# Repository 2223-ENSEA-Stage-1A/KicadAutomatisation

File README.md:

# KicadAutomatisation
Tous les scripts pour les automatisations kicad

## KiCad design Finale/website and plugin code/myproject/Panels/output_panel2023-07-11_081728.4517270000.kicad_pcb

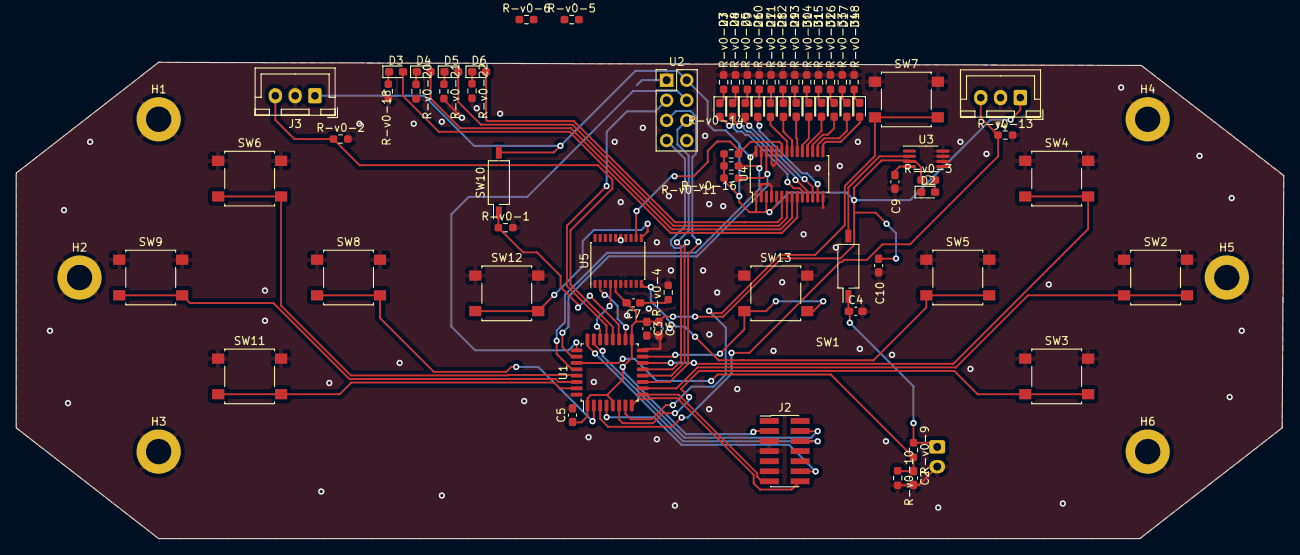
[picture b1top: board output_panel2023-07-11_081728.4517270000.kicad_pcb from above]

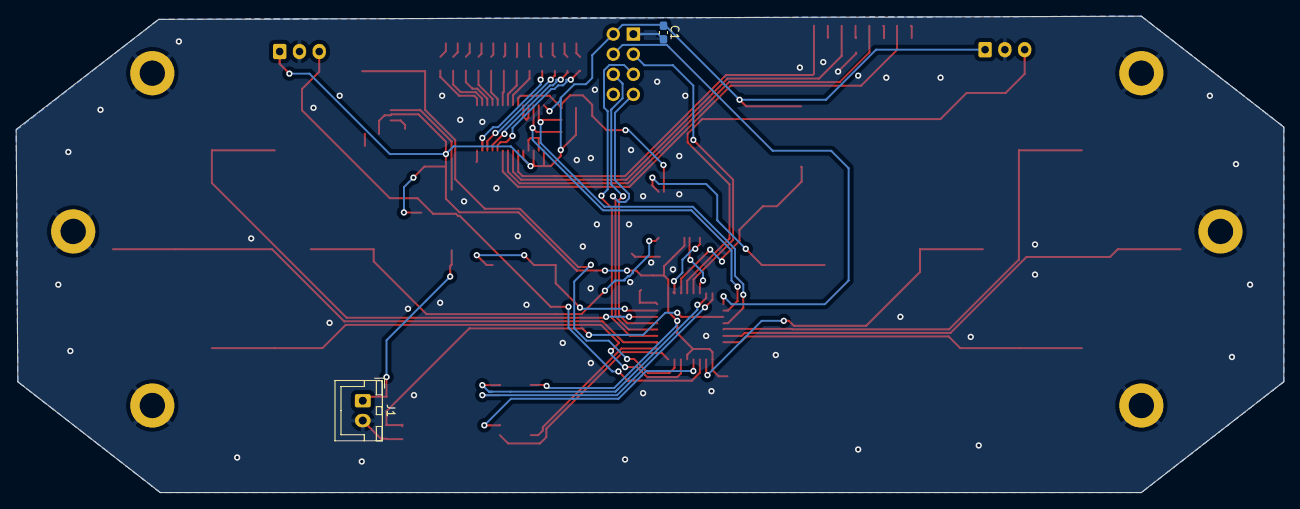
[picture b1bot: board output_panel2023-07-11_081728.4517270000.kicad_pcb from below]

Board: 2 copper layers, 160.2 x 60.2 mm, 82 parts (2 on the bottom side), 69 nets.

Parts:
C1: 100uF; C_0603_1608Metric_Pad1.08x0.95mm_HandSolder
C2: 1nF; C_0603_1608Metric_Pad1.08x0.95mm_HandSolder
C3, C5: 100n; C_0603_1608Metric_Pad1.08x0.95mm_HandSolder
C4: 1u; C_0603_1608Metric_Pad1.08x0.95mm_HandSolder
C6: 10u; C_0603_1608Metric_Pad1.08x0.95mm_HandSolder
C7: 100µF; C_0603_1608Metric_Pad1.08x0.95mm_HandSolder
C9: 470p; C_0603_1608Metric_Pad1.08x0.95mm_HandSolder
C10: 100nF; C_0603_1608Metric_Pad1.08x0.95mm_HandSolder
D2: L-v0-ED_Small; L-v0-ED_0603_1608Metric_Pad1.05x0.95mm_HandSolder
D3: G1; L-v0-ED_0603_1608Metric_Pad1.05x0.95mm_HandSolder
D4: G2; L-v0-ED_0603_1608Metric_Pad1.05x0.95mm_HandSolder
D5: G3; L-v0-ED_0603_1608Metric_Pad1.05x0.95mm_HandSolder
D6: G4; L-v0-ED_0603_1608Metric_Pad1.05x0.95mm_HandSolder
D7: G5; L-v0-ED_0603_1608Metric_Pad1.05x0.95mm_HandSolder
D8: G6; L-v0-ED_0603_1608Metric_Pad1.05x0.95mm_HandSolder
D9: G7; L-v0-ED_0603_1608Metric_Pad1.05x0.95mm_HandSolder
D10: G8; L-v0-ED_0603_1608Metric_Pad1.05x0.95mm_HandSolder
D11: O1; L-v0-ED_0603_1608Metric_Pad1.05x0.95mm_HandSolder
D12: O2; L-v0-ED_0603_1608Metric_Pad1.05x0.95mm_HandSolder
D13: O3; L-v0-ED_0603_1608Metric_Pad1.05x0.95mm_HandSolder
D14: O4; L-v0-ED_0603_1608Metric_Pad1.05x0.95mm_HandSolder
D15: R-v0-1; L-v0-ED_0603_1608Metric_Pad1.05x0.95mm_HandSolder
D16: R-v0-2; L-v0-ED_0603_1608Metric_Pad1.05x0.95mm_HandSolder
D17: R-v0-3; L-v0-ED_0603_1608Metric_Pad1.05x0.95mm_HandSolder
D18: R-v0-4; L-v0-ED_0603_1608Metric_Pad1.05x0.95mm_HandSolder
H1, H2, H3, H4, H5, H6: MountingHole_Pad; MountingHole_3.2mm_M3_DIN965_Pad
J1: Conn_01x02; JST_XH_B2B-XH-A_1x02_P2.50mm_Vertical
J2: Conn_02x07_Odd_Even; PinHeader_2x07_P1.27mm_Vertical_SMD
J3, J4: Conn_01x03; JST_XH_B3B-XH-A_1x03_P2.50mm_Vertical
R-v0-1, R-v0-2, R-v0-3, R-v0-5, R-v0-6, R-v0-13, R-v0-18, R-v0-20, R-v0-21, R-v0-22, R-v0-23, R-v0-24, R-v0-25, R-v0-26, R-v0-27, R-v0-28, R-v0-29, R-v0-30, R-v0-31, R-v0-32, R-v0-33, R-v0-34: 1K; R-v0-_0603_1608Metric_Pad0.98x0.95mm_HandSolder
R-v0-4: 10k; R-v0-_0603_1608Metric_Pad0.98x0.95mm_HandSolder
R-v0-9, R-v0-10: 1M; R-v0-_0603_1608Metric_Pad0.98x0.95mm_HandSolder
R-v0-11, R-v0-14, R-v0-16: 10K; R-v0-_0603_1608Metric_Pad0.98x0.95mm_HandSolder
SW1, SW10: SW_DIP_x01; SW_DIP_SPSTx01_Slide_Copal_CHS-01B_W7.62mm_P1.27mm
SW2, SW3, SW4, SW5, SW6, SW8, SW9, SW11, SW12, SW13: SW_Push; SW_SPST_B3S-1000
SW7: SW_SPST; SW_SPST_B3S-1000
U1: STM32L-v0-412KBTx; L-v0-QFP-32_7x7mm_P0.8mm
U2: nR-v0-F24_Full; PinHeader_2x04_P2.54mm_Vertical
U3: MIC5219-3.3YMM; MSOP-8_3x3mm_P0.65mm
U4: PCA9685PW; TSSOP-28_4.4x9.7mm_P0.65mm
U5: PCF8574TS; SSOP-20_4.4x6.5mm_P0.65mm

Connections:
A_Button-v0-: SW2.2, U1.10 (PA4)
B_Button-v0-: SW3.2, U1.6 (PA0)
CSN_nR-v0-F24: U1.25 (PA15), U2.4 (CSN)
DC_Button-v0-: SW11.2, U1.31 (PH3)
DIODE_CL-v0-K: R-v0-14.2, U1.26 (PB3), U4.26 (SCL-v0-)
DIODE_OE-v0-: R-v0-16.1, U4.23 (~OE), U5.12 (P2)
DIODE_SDA-v0-: R-v0-11.1, U1.28 (PB5), U4.27 (SDA)
Digital_Out_Put-v0-: U1.12 (PA6), U2.7 (MISO)
GND-v0-: C1.2, C2.2, C3.2, C4.2, C5.2, C6.2, C9.2, C10.2, D2.1 (K), H1.1, H2.1, H3.1, H4.1, H5.1, H6.1, J1.2, J2.5, J2.7, J2.11, J3.2, J4.2, R-v0-1.2, R-v0-2.2, R-v0-4.2, R-v0-10.2, R-v0-13.2, R-v0-18.2, R-v0-20.2, R-v0-21.2, R-v0-22.2, R-v0-23.2, R-v0-24.2, R-v0-25.2, R-v0-26.2, R-v0-27.2, R-v0-28.2, R-v0-29.2, R-v0-30.2, R-v0-31.2, R-v0-32.2, R-v0-33.2, R-v0-34.2, SW2.1, SW3.1, SW4.1, SW5.1, SW6.1, SW7.1 (A), SW8.1, SW9.1, SW11.1, SW12.1, SW13.1, U1.16 (VSS), U1.32 (VSS), U2.1 (GND-v0-), U3.5 (GND-v0-), U3.6 (GND-v0-), U3.7 (GND-v0-), U3.8 (GND-v0-), U4.2 (A1), U4.4 (A3), U4.14 (VSS), U4.24 (A5), U4.25 (EXTCL-v0-K), U5.1 (~INT), U5.6 (A0), U5.7 (A1), U5.9 (A2), U5.15 (VSS)
GPIO_EX_CL-v0-K: R-v0-5.2, U1.18 (PA8), U5.2 (SCL-v0-)
GPIO_EX_SER-v0-IAL-v0-_DATA: R-v0-6.2, U1.22 (PA12), U5.4 (SDA)
Glob_Alim-v0-: C1.1, C3.1, C5.1, C6.1, C7.2, C10.1, J2.3, J3.1, J4.1, R-v0-3.1, R-v0-5.1, R-v0-6.1, R-v0-11.2, R-v0-14.1, R-v0-16.2, SW10.2, U1.1 (VDD), U1.5 (VDDA), U1.17 (VDD), U2.2 (VCC), U3.3 (OUT), U4.1 (A0), U4.3 (A2), U4.5 (A4), U4.28 (VDD), U5.5 (VDD)
L-v0-: J4.3, R-v0-13.1, U1.3 (PC15)
L-v0-C_Button-v0-: SW8.2, U1.2 (PC14)
L-v0-i-ion-v0-: C4.1, J1.1, R-v0-9.1, SW1.1
MOSI-v0-: U1.13 (PA7), U2.6 (MOSI-v0-)
NES/SNES_switcher-v0-: R-v0-1.1, SW10.1, U1.19 (PA9)
unnamed: C7.1, R-v0-4.1
unnamed: D2.2 (A), R-v0-3.2
unnamed: D3.2 (A), U4.9 (L-v0-ED3)
unnamed: D3.1 (K), R-v0-18.1
unnamed: D4.2 (A), U4.8 (L-v0-ED2)
unnamed: D4.1 (K), R-v0-20.1
unnamed: D5.2 (A), U4.7 (L-v0-ED1)
unnamed: D5.1 (K), R-v0-21.1
unnamed: D6.2 (A), U4.6 (L-v0-ED0)
unnamed: D6.1 (K), R-v0-22.1
unnamed: D7.2 (A), U4.10 (L-v0-ED4)
unnamed: D7.1 (K), R-v0-23.1
unnamed: D8.2 (A), U4.11 (L-v0-ED5)
unnamed: D8.1 (K), R-v0-24.1
unnamed: D9.2 (A), U4.12 (L-v0-ED6)
unnamed: D9.1 (K), R-v0-25.1
unnamed: D10.2 (A), U4.13 (L-v0-ED7)
unnamed: D10.1 (K), R-v0-26.1
unnamed: D11.2 (A), U4.22 (L-v0-ED15)
unnamed: D11.1 (K), R-v0-27.1
unnamed: D12.2 (A), U4.21 (L-v0-ED14)
unnamed: D12.1 (K), R-v0-28.1
unnamed: D13.2 (A), U4.20 (L-v0-ED13)
unnamed: D13.1 (K), R-v0-29.1
unnamed: D14.2 (A), U4.19 (L-v0-ED12)
unnamed: D14.1 (K), R-v0-30.1
unnamed: D15.2 (A), U4.18 (L-v0-ED11)
unnamed: D15.1 (K), R-v0-31.1
unnamed: D16.2 (A), U4.17 (L-v0-ED10)
unnamed: D16.1 (K), R-v0-32.1
unnamed: D17.2 (A), U4.16 (L-v0-ED9)
unnamed: D17.1 (K), R-v0-33.1
unnamed: D18.2 (A), U4.15 (L-v0-ED8)
unnamed: D18.1 (K), R-v0-34.1
unnamed: C9.1, U3.4 (BP)
unnamed: SW1.2, U3.2 (IN)
Order_Search-v0-: SW7.2 (B), U1.7 (PA1)
POWER-v0-_CHECK-v0-: C2.1, R-v0-9.2, R-v0-10.1, U1.27 (PB4)
Pin_Clock-v0-: U1.11 (PA5), U2.5 (SCK)
R-v0-: J3.3, R-v0-2.1, U1.20 (PA10)
R-v0-C_Button: SW9.2, U1.30 (PB7)
R-v0-X/TX: U1.21 (PA11), U2.3 (CE)
R-v0-eset_Buton -v0-: J2.12, U1.4 (NR-v0-ST)
SE_Button-v0-: SW13.2, U1.15 (PB1)
ST_Button-v0-: SW12.2, U5.11 (P1)
SWDCK-v0-: J2.6, U1.24 (PA14)
SWDIO-v0-: J2.4, U1.23 (PA13)
UC_Button-v0-: SW6.2, U1.29 (PB6)
USAR-v0-T2_R-v0-X-v0-: J2.13, U1.9 (PA3)
USAR-v0-T2_TX-v0-: J2.14, U1.8 (PA2)
X_Button-v0-: SW4.2, U1.14 (PB0)
Y_Button-v0-: SW5.2, U5.10 (P0)

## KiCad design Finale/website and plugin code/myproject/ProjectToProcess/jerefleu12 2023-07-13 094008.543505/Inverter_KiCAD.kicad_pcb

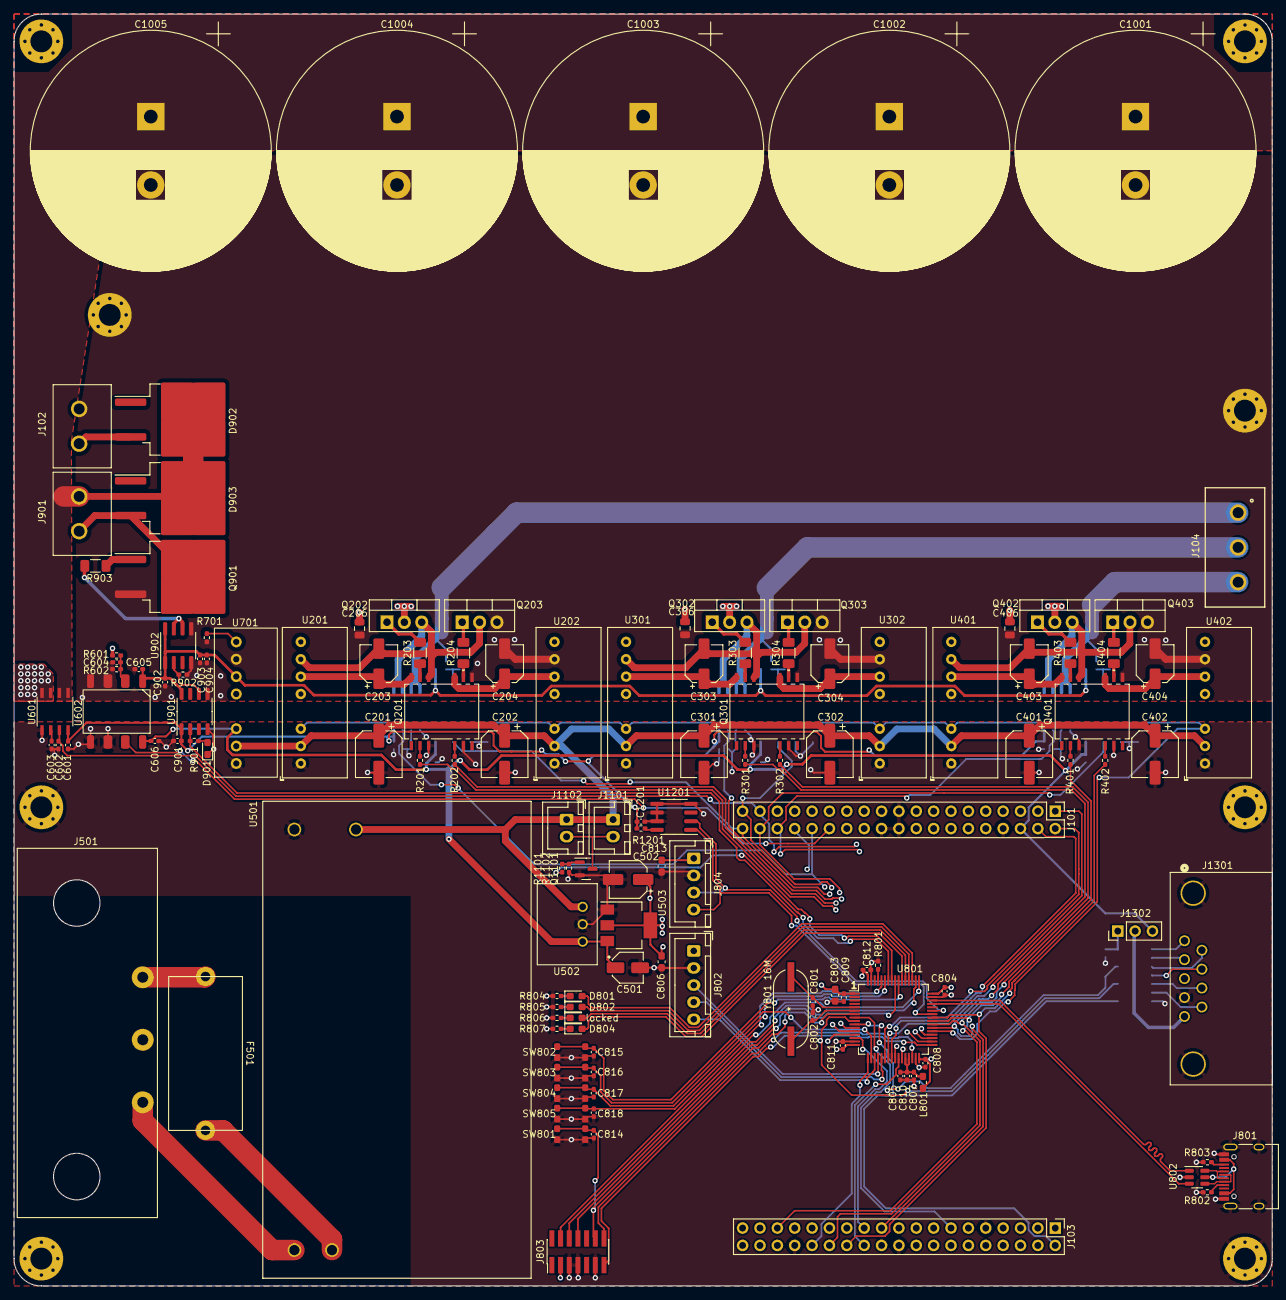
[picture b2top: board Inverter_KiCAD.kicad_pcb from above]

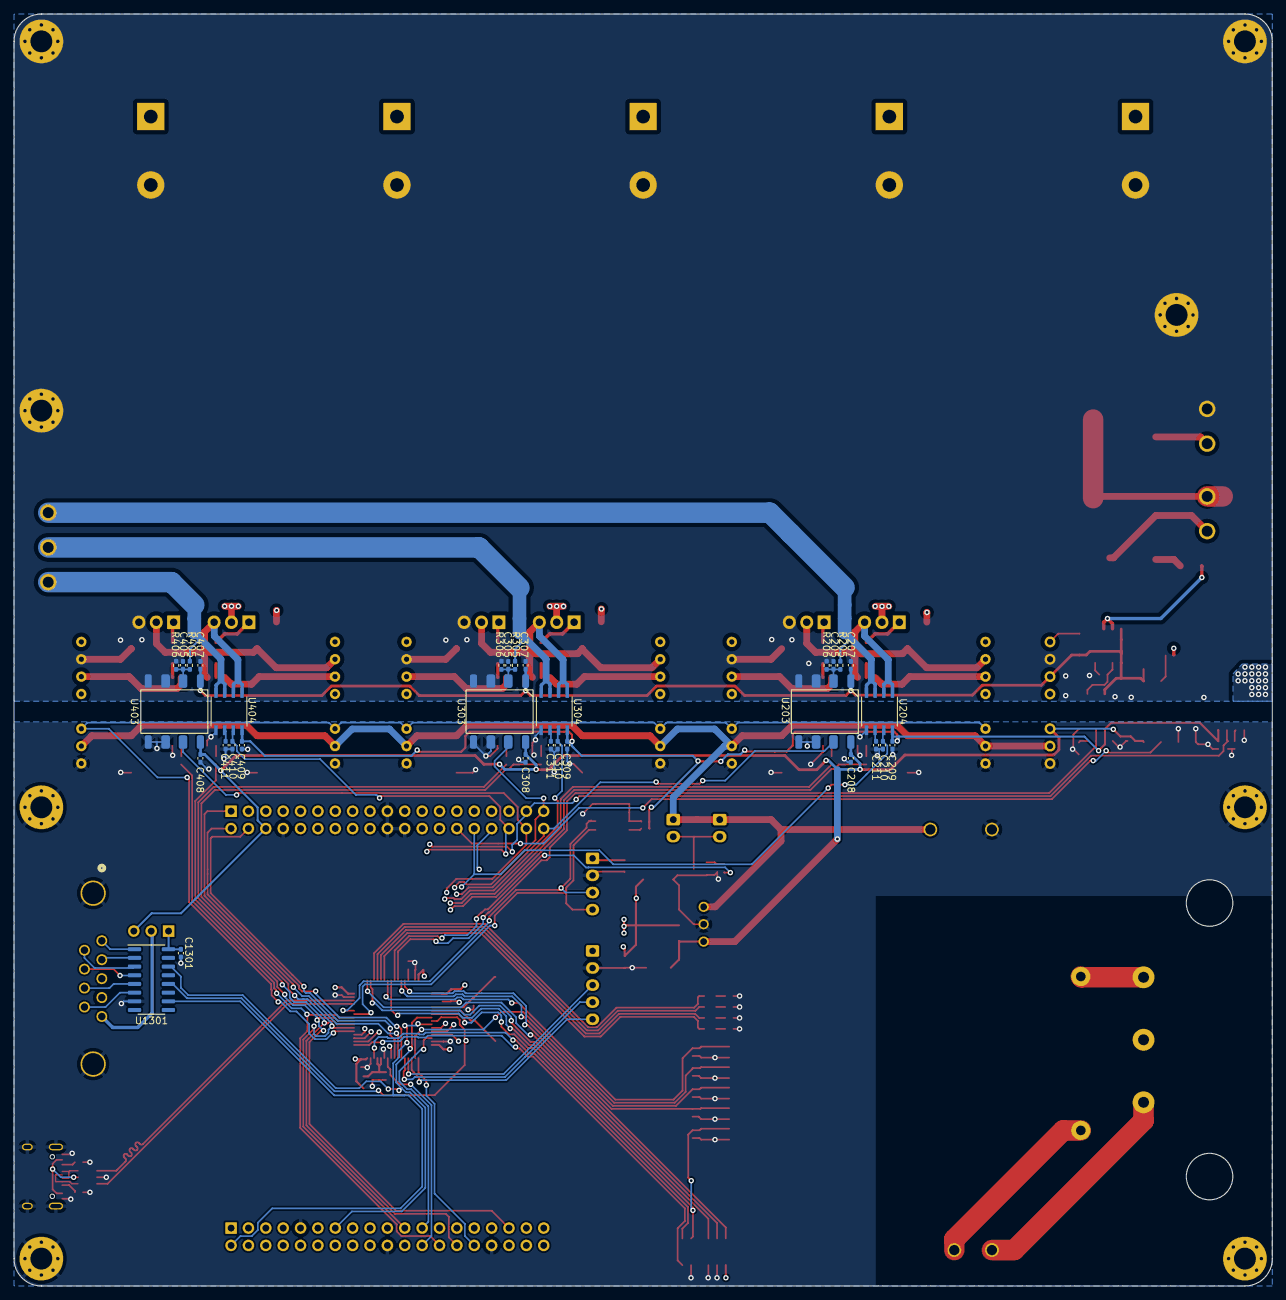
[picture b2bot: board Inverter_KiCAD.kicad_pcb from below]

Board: 4 copper layers, 184.0 x 186.0 mm, 176 parts (32 on the bottom side), 123 nets.

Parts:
C201, C202, C301, C302, C401, C402: 100u; CP_Elec_6.3x7.7
C203, C204, C303, C304, C403, C404, C502: 22u; CP_Elec_5x5.4
C205, C305, C405, C604: 10n; C_0402_1005Metric_Pad0.74x0.62mm_HandSolder
C206, C306, C406: 10u; C_0805_2012Metric
C207, C208, C307, C308, C407, C408, C605, C606, C804, C807, C808, C809, C810, C811, C812, C814, C815, C816, C817, C818, C901, C902, C1201, C1301: 100n; C_0402_1005Metric_Pad0.74x0.62mm_HandSolder
C209, C210, C211, C309, C310, C311, C409, C410, C411, C601, C602, C603: 4.7n; C_0402_1005Metric_Pad0.74x0.62mm_HandSolder
C501: 10u; CP_Elec_4x5.4
C801, C802: 18p; C_0402_1005Metric_Pad0.74x0.62mm_HandSolder
C803, C806, C813: 10u; C_0603_1608Metric_Pad1.08x0.95mm_HandSolder
C805, C903: 1u; C_0402_1005Metric_Pad0.74x0.62mm_HandSolder
C904: 1n; C_0402_1005Metric_Pad0.74x0.62mm_HandSolder
C1001, C1002, C1003, C1004, C1005: 1.5m; CP_Radial_D35.0mm_P10.00mm_SnapIn
D801, D802, D804: LED; LED_0603_1608Metric_Pad1.05x0.95mm_HandSolder
D901: Red; LED_0603_1608Metric_Pad1.05x0.95mm_HandSolder
D902, D903: VS-15TQ060S-M3; TO-263-2
F501: Fuse; 0031.8201
H101, H102, H103, H104, H105, H106, H107, H108: MountingHole_Pad; MountingHole_3.2mm_M3_Pad_Via
J101, J103: Conn_02x19_Odd_Even; PinHeader_2x19_P2.54mm_Vertical
J102, J901: Conn_01x02; 691311500102
J104: Conn_01x03; 691311500103
J501: PX0580-PC-12132
J801: USB_C_Receptacle_USB2.0; USB_C_Receptacle_HRO_TYPE-C-31-M-12
J802: Conn_01x05; JST_XH_B5B-XH-A_1x05_P2.50mm_Vertical
J803: Conn_ST_STDC14; PinHeader_2x07_P1.27mm_Vertical_SMD
J804: Conn_01x04; JST_XH_B4B-XH-A_1x04_P2.50mm_Vertical
J1101, J1102: Conn_01x02; JST_XH_B2B-XH-A_1x02_P2.50mm_Vertical
J1301: DE9_Receptacle_MountingHoles; 618009233821
J1302: Conn_01x03; PinHeader_1x03_P2.54mm_Vertical
L801: 39n; L_0603_1608Metric_Pad1.05x0.95mm_HandSolder
Q201, Q301, Q401: HCPL-315J-500E; SO-16_HCPL-315J_BRA
Q202, Q203, Q302, Q303, Q402, Q403: IRF540N; TO-220-3_Vertical
Q901: BUK9637-100E; TO-263-2
Q1101: SQ2310ES; SOT-23
R201, R202, R301, R302, R401, R402: 170; R_0402_1005Metric_Pad0.72x0.64mm_HandSolder
R203, R204, R303, R304, R403, R404: 30; R_1206_3216Metric_Pad1.30x1.75mm_HandSolder
R205, R305, R405, R601: 160k; R_0402_1005Metric_Pad0.72x0.64mm_HandSolder
R206, R306, R406, R602: 1k; R_0402_1005Metric_Pad0.72x0.64mm_HandSolder
R701: 27k; R_0402_1005Metric_Pad0.72x0.64mm_HandSolder
R801, R902, R1102: 10k; R_0402_1005Metric_Pad0.72x0.64mm_HandSolder
R802, R803: 5.1k; R_0402_1005Metric_Pad0.72x0.64mm_HandSolder
R804, R805, R806, R807: 340; R_0402_1005Metric_Pad0.72x0.64mm_HandSolder
R901: 100; R_0402_1005Metric_Pad0.72x0.64mm_HandSolder
R903: 5; R_1206_3216Metric_Pad1.30x1.75mm_HandSolder
R1101: 22; R_0402_1005Metric_Pad0.72x0.64mm_HandSolder
R1201: 200; R_0402_1005Metric_Pad0.72x0.64mm_HandSolder
SW801, SW802, SW803, SW804, SW805: SW_Push; 435451019820
U201, U202, U301, U302, U401, U402: MPRB2415S-6W; MPRB2415S
U203, U303, U403, U602: HCPL-7800-500E; DIP-8 Gull Wing
U204, U304, U404, U601: GO 10-SME/SP3; SOIC8-GO-SME&slash_SP3_LEM
U501: MP-LD30-23B12R2; MP-LD30-23B15R2
U502: 173010542; 173010578
U503: AZ1117-3.3; SOT-223-3_TabPin2
U701: 17791063215
U801: STM32G474RETx; LQFP-64_10x10mm_P0.5mm
U802: USBLC6-2SC6; SOT-23-6
U901: ACPL-077L; SO-8_3.9x4.9mm_P1.27mm
U902: TC1412; SOIC-8_3.9x4.9mm_P1.27mm
U1201: TCN75A; SOIC-8_3.9x4.9mm_P1.27mm
U1301: MAX3097ECSE+; SOIC-16_3.9x9.9mm_P1.27mm
Y801: 16M; ABLS-7.3728MHZ-CL-RESR-A-1-G-F
locked: LED; LED_0603_1608Metric_Pad1.05x0.95mm_HandSolder

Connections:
/5V: C207.1, C307.1, C407.1, C605.1, C902.1, C903.1, C904.1, U203.1 (VDD1), U303.1 (VDD1), U403.1 (VDD1), U602.1 (VDD1), U701.6 (Vout), U901.8 (VDD2), U902.1 (VDD), U902.8 (VDD)
/Arm_IRF540NBbF1/ARM_OUT: C303.2, Q301.14 (VEE), Q302.3 (S), Q303.2 (D), U301.7 (0V), U304.1 (IP+), U304.2 (IP+)
/Arm_IRF540NBbF1/Cmd_H: Q302.1 (G), R303.2
/Arm_IRF540NBbF1/Cmd_L: Q303.1 (G), R304.2
/Arm_IRF540NBbF1/Uref: C311.1, U304.6 (UREF)
/Arm_IRF540NBbF1/VCC_H: C303.1, Q301.16 (VCC), U301.6 (Vout)
/Arm_IRF540NBbF1/VCC_L: C304.1, Q301.11 (VCC), U302.6 (Vout)
/Arm_IRF540NBbF2/ARM_OUT: C403.2, Q401.14 (VEE), Q402.3 (S), Q403.2 (D), U401.7 (0V), U404.1 (IP+), U404.2 (IP+)
/Arm_IRF540NBbF2/Cmd_H: Q402.1 (G), R403.2
/Arm_IRF540NBbF2/Cmd_L: Q403.1 (G), R404.2
/Arm_IRF540NBbF2/Uref: C411.1, U404.6 (UREF)
/Arm_IRF540NBbF2/VCC_H: C403.1, Q401.16 (VCC), U401.6 (Vout)
/Arm_IRF540NBbF2/VCC_L: C404.1, Q401.11 (VCC), U402.6 (Vout)
/Arm_IRF540NBbF/ARM_OUT: C203.2, Q201.14 (VEE), Q202.3 (S), Q203.2 (D), U201.7 (0V), U204.1 (IP+), U204.2 (IP+)
/Arm_IRF540NBbF/Cmd_H: Q202.1 (G), R203.2
/Arm_IRF540NBbF/Cmd_L: Q203.1 (G), R204.2
/Arm_IRF540NBbF/Uref: C211.1, U204.6 (UREF)
/Arm_IRF540NBbF/VCC_H: C203.1, Q201.16 (VCC), U201.6 (Vout)
/Arm_IRF540NBbF/VCC_L: C204.1, Q201.11 (VCC), U202.6 (Vout)
/Bus_Imes: C602.1, J101.35, U601.7 (UOUT), U801.36 (PB14)
/Bus_V: J101.28, U602.7 (VOUT+), U801.34 (PB12)
/ENC_A: J103.13, U801.8 (PC0), U1301.14 (OutA)
/ENC_B: J101.32, U801.9 (PC1), U1301.12 (OutB)
/ENC_Z: J103.2, U801.10 (PC2), U1301.10 (OutZ)
/I2C_SCL: J804.3, U801.43 (PA9), U1201.2 (SCL)
/I2C_SDA: J804.4, U801.42 (PA8), U1201.1 (SDA)
/ISO_3V3: C209.1, C309.1, C409.1, C502.1, C601.1, C803.1, C804.1, C806.2, C808.1, C809.1, C811.1, C812.1, C813.1, C901.1, C1201.1, C1301.1, J802.1, J803.3 (VCC), J804.1, J1302.1, L801.1, R1201.2, U204.8 (UC), U304.8 (UC), U404.8 (UC), U503.2 (VO), U601.8 (UC), U801.1 (VBAT), U801.16 (VDD), U801.32 (VDD), U801.48 (VDD), U801.64 (VDD), U901.1 (VDD1), U1301.16 (VCC)
/ISO_5V: C208.1, C308.1, C408.1, C501.1, C606.1, J101.6, J1302.3, U203.8 (VDD2), U303.8 (VDD2), U403.8 (VDD2), U502.3 (5V), U503.3 (VI), U602.8 (VDD2), U701.3 (Ctrl)
/ISO_15V: C201.1, C202.1, C301.1, C302.1, C401.1, C402.1, J1101.1, J1102.1, U201.2 (Vin), U202.2 (Vin), U301.2 (Vin), U302.2 (Vin), U401.2 (Vin), U402.2 (Vin), U501.3 (+15V), U502.1 (VIN), U701.2 (Vin)
/ISO_GND: C201.2, C202.2, C208.2, C209.2, C210.2, C211.2, C301.2, C302.2, C308.2, C309.2, C310.2, C311.2, C401.2, C402.2, C408.2, C409.2, C410.2, C411.2, C501.2, C502.2, C601.2, C602.2, C603.2, C606.2, C801.1, C802.1, C803.2, C804.2, C805.2, C806.1, C807.2, C808.2, C809.2, C810.2, C811.2, C812.2, C813.2, C814.2, C815.2, C816.2, C817.2, C818.2, C901.2, C1201.2, C1301.2, D901.1 (K), H102.1, H103.1, H104.1, J101.8, J101.19, J101.20, J101.22, J103.9, J103.20, J103.32, J801.A1 (GND), J801.A12 (GND), J801.B1 (GND), J801.B12 (GND), J801.S1 (SHIELD), J802.2, J803.5 (GND), J803.7 (GND), J803.11 (GNDDetect), J804.2, J1301.4, J1301.10 (PAD), Q201.3 (Cathode), Q201.7 (Cathode), Q301.3 (Cathode), Q301.7 (Cathode), Q401.3 (Cathode), Q401.7 (Cathode), Q1101.2 (S), R801.2, R802.2, R803.2, R804.2, R805.2, R806.2, R807.2, R1102.2, SW801.2, SW802.2, SW803.2, SW804.2, SW805.2, U201.1 (GND), U202.1 (GND), U203.5 (GND2), U203.6 (VOUT-), U204.5 (GND), U301.1 (GND), U302.1 (GND), U303.5 (GND2), U303.6 (VOUT-), U304.5 (GND), U401.1 (GND), U402.1 (GND), U403.5 (GND2), U403.6 (VOUT-), U404.5 (GND), U501.4 (GND), U502.2 (GND), U503.1 (GND), U601.5 (GND), U602.5 (GND2), U602.6 (VOUT-), U701.1 (Vin_GND), U801.15 (VSS), U801.27 (VSSA), U801.31 (VSS), U801.47 (VSS), U801.63 (VSS), U802.2 (GND), U901.4 (GND1), U1201.4 (GND), U1201.5 (A2), U1201.6 (A1), U1201.7 (A0), U1301.7 (GND)
/ISO_PWM_Break: R901.1, U801.58 (PB5), U901.2 (In)
/ISO_PWM_FAN: R1101.2, U801.57 (PB4)
/MCU_STM32G474/D+: J801.A6 (D+), J801.B6 (D+), U802.6 (I/O1)
/MCU_STM32G474/D-: J801.A7 (D-), J801.B7 (D-), U802.4 (I/O2)
/MCU_STM32G474/ENC_BTN_A: J802.3, U801.20 (PA6)
/MCU_STM32G474/ENC_BTN_B: J802.4, U801.21 (PA7)
/MCU_STM32G474/ENC_BTN_P: J802.5, U801.19 (PA5)
/MCU_STM32G474/ISO_3V3A: C805.1, C807.1, C810.1, L801.2, U801.28 (VREF+), U801.29 (VDDA)
/MCU_STM32G474/NRST: C814.1, J803.12 (~RST), SW801.1, U801.7 (PG10)
/MCU_STM32G474/SWCLK: J803.6 (JCLK/SWCLK), U801.50 (PA14)
/MCU_STM32G474/SWDIO: J803.4 (JTMS/SWDIO), U801.49 (PA13)
/MCU_STM32G474/SWO: J803.8 (JTDO/SWO), U801.56 (PB3)
/MCU_STM32G474/Soft_NRST: C818.1, SW805.1, U801.60 (PB7)
/MCU_STM32G474/USB_DM: U801.45 (PA11), U802.3 (I/O2)
/MCU_STM32G474/USB_DP: U801.46 (PA12), U802.1 (I/O1)
/MCU_STM32G474/USR_BTN_1: C815.1, SW802.1, U801.55 (PD2)
/MCU_STM32G474/USR_BTN_2: C816.1, SW803.1, U801.18 (PA4)
/MCU_STM32G474/USR_BTN_3: C817.1, SW804.1, U801.59 (PB6)
/MCU_STM32G474/USR_LED_1: D801.2 (A), U801.51 (PA15)
/MCU_STM32G474/USR_LED_2: D802.2 (A), U801.52 (PC10)
/MCU_STM32G474/USR_LED_3: U801.53 (PC11), locked.2 (A)
/MCU_STM32G474/USR_LED_4: D804.2 (A), U801.54 (PC12)
/MCU_STM32G474/VCP_RX: J803.13 (VCP_RX), U801.33 (PB11)
/MCU_STM32G474/VCP_TX: J803.14 (VCP_TX), U801.30 (PB10)
/MCU_STM32G474/V_USB: J801.A4 (VBUS), J801.A9 (VBUS), J801.B4 (VBUS), J801.B9 (VBUS), U802.5 (VBUS)
/NUCLEO_NRST: J101.4, U801.24 (PB0)
/NUCLEO_RX: J101.2, U801.22 (PC4)
/NUCLEO_TX: J101.1, U801.23 (PC5)
/Pwr_En: U201.3 (Ctrl), U202.3 (Ctrl), U301.3 (Ctrl), U302.3 (Ctrl), U401.3 (Ctrl), U402.3 (Ctrl), U801.37 (PB15)
/U_Imes: C210.1, J101.30, U204.7 (UOUT), U801.13 (PA1)
/U_PWM_H: J103.23, R201.2, U801.14 (PA2)
/U_PWM_L: J103.30, R202.2, U801.17 (PA3)
/U_VPh: J101.38, U203.7 (VOUT+), U801.12 (PA0)
/U_output: J104.1, R205.1, U204.3 (IP-), U204.4 (IP-)
/VSupply_AB: C1001.1, C1002.1, C1003.1, C1004.1, C1005.1, D902.2 (K), D903.2 (K), J901.2, U601.1 (IP+), U601.2 (IP+)
/VSupply_BB: D902.3 (A), J102.1
/V_Imes: C310.1, J103.24, U304.7 (UOUT), U801.26 (PB2)
/V_PWM_H: J103.21, R301.2, U801.38 (PC6)
/V_PWM_L: J103.28, R302.2, U801.39 (PC7)
/V_VPh: J101.37, U303.7 (VOUT+), U801.11 (PC3)
/V_output: J104.2, R305.1, U304.3 (IP-), U304.4 (IP-)
/Vbus: C206.1, C306.1, C406.1, Q202.2 (D), Q302.2 (D), Q402.2 (D), R601.1, U601.3 (IP-), U601.4 (IP-)
/Vbus_Sense/Uref: C603.1, U601.6 (UREF)
/W_Imes: C410.1, J101.34, U404.7 (UOUT), U801.35 (PB13)
/W_PWM_H: J103.33, R401.2, U801.40 (PC8)
/W_PWM_L: J103.26, R402.2, U801.41 (PC9)
/W_VPh: J101.36, U403.7 (VOUT+), U801.25 (PB1)
/W_output: J104.3, R405.1, U404.3 (IP-), U404.4 (IP-)
/break/Break_Drain_Mosfet: D903.3 (A), J901.1, Q901.2 (D)
/break/PWM_Break: R902.1, U901.6 (Out), U902.2 (IN)
/break/PWM_Mosfet: R903.1, U902.6 (OUT), U902.7 (OUT)
/encoderMotor/A: J1301.1, U1301.1 (A)
/encoderMotor/B: J1301.6, U1301.3 (B)
/encoderMotor/VCC_Enc: J1301.5, J1302.2
/encoderMotor/Z: J1301.8, U1301.5 (Z)
/encoderMotor//A: J1301.2, U1301.2 (/A)
/encoderMotor//B: J1301.7, U1301.4 (/B)
/encoderMotor//Z: J1301.9, U1301.6 (/Z)
GND: C204.2, C205.2, C206.2, C207.2, C304.2, C305.2, C306.2, C307.2, C404.2, C405.2, C406.2, C407.2, C604.2, C605.2, C902.2, C903.2, C904.2, C1001.2, C1002.2, C1003.2, C1004.2, C1005.2, H105.1, H106.1, H107.1, H108.1, J102.2, Q201.9 (VEE), Q203.3 (S), Q301.9 (VEE), Q303.3 (S), Q401.9 (VEE), Q403.3 (S), Q901.3 (S), R206.2, R306.2, R406.2, R602.2, R701.2, R902.2, U202.7 (0V), U203.3 (VIN-), U203.4 (GND1), U302.7 (0V), U303.3 (VIN-), U303.4 (GND1), U402.7 (0V), U403.3 (VIN-), U403.4 (GND1), U602.3 (VIN-), U602.4 (GND1), U701.7 (Vout_Gnd), U901.5 (GND2), U902.4 (GND), U902.5 (GND)
unnamed: D801.1 (K), R804.1
unnamed: D802.1 (K), R805.1
unnamed: R806.1, locked.1 (K)
unnamed: D804.1 (K), R807.1
unnamed: D901.2 (A), R901.2
unnamed: F501.1, J501.3 (L)
unnamed: J501.1 (N), U501.1 (AC(L))
unnamed: J801.A5 (CC1), R802.1
unnamed: J801.B5 (CC2), R803.1
unnamed: J1101.2, J1102.2, Q1101.3 (D)
unnamed: Q201.2 (Anode), R201.1
unnamed: Q201.6 (Anode), R202.1
unnamed: Q201.10 (Vo), R204.1
unnamed: Q201.15 (Vo), R203.1
unnamed: Q301.2 (Anode), R301.1
unnamed: Q301.6 (Anode), R302.1
unnamed: Q301.10 (Vo), R304.1
unnamed: Q301.15 (Vo), R303.1
unnamed: Q401.2 (Anode), R401.1
unnamed: Q401.6 (Anode), R402.1
unnamed: Q401.10 (Vo), R404.1
unnamed: Q401.15 (Vo), R403.1
unnamed: Q901.1 (G), R903.2
unnamed: Q1101.1 (G), R1101.1, R1102.1
unnamed: C205.1, R205.2, R206.1, U203.2 (VIN+)
unnamed: C305.1, R305.2, R306.1, U303.2 (VIN+)
unnamed: C405.1, R405.2, R406.1, U403.2 (VIN+)
unnamed: F501.2, U501.2 (AC(N))
unnamed: C604.1, R601.2, R602.1, U602.2 (VIN+)
unnamed: R701.1, U701.8 (FB)
unnamed: R801.1, U801.61 (PB8)
unnamed: C801.2, U801.5 (PF0), Y801.2
unnamed: C802.2, U801.6 (PF1), Y801.1
unnamed: R1201.1, U1201.8 (VDD)

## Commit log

2023-06-13 Premier code qui marche qui fait des gerber
    Je sais pas si c'est les bon gerber ^^ mais au moins ça ressemble à quelque chose ^^
2023-06-13 fichier gerber et drl
    Il fait en plus des gerber, les drills ^^aucune vérification pour le moment
2023-06-15 Organisation 101
    Organisation du git ^^
2023-06-16 working website v1
    Only taking care of submitting file and running drc, erc on them and then generating their gerber and drill files
2023-06-16 Class check and website improved
    Only handle kicad project.
2023-06-19 Website working v2
    Taking clearance into consideration when evaluating pcb class
2023-06-19 Website working v3
    Parsing of the output, so that errors and warnings are displayed understandably by users
2023-06-20 A new interface to select stuff
    new interface, using a database to handle downloaded file. and allowing users to delete their own project
2023-06-20 View button were bugged
    download of the file upon click
2023-06-20 patricia interface
    Interface admin
2023-06-21 Fur Elise
    Fur Elise
2023-06-23 Panelizer and interface after it
    A panelizer that takes care of rectangular PCB
2023-06-26 Working panelizer and interface
    beautiful work
2023-06-27 Working panelizer and other bug fix
    various bug fix
2023-06-27 Working panelize ++ with otimized placment
    happy thouht
2023-06-29 working stuff
    stuff
2023-06-29 Kicad deposit improved, somewhat atleast
    handle validity and error for user
2023-07-06 rdftgdfg
    sfgsg
2023-07-10 The end ?
    Enter the end
2023-07-10 docker friendly
    docker friendly
2023-07-10 ptdr t ki ?
    ptdr t ki ?
2023-07-11 v3 ?
    ouais ...
2023-07-11 v3.
    fr
2023-07-12 finished for real ^^
    C'est la fin ! Vive les vacances !
2023-07-12 kdo
    kdo
    doc
2023-07-13 Final version ready for prod
    Final version ready for prod with errors handling capabilities.
